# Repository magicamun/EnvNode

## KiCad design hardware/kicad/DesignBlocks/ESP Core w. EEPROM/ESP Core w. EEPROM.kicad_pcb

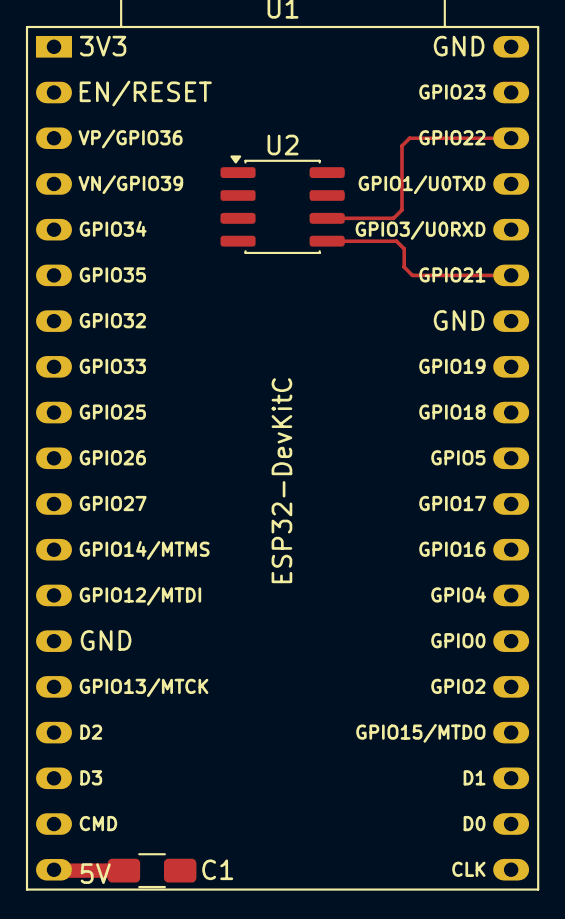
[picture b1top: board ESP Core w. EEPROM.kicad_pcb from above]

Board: 2 copper layers, 3 parts (0 on the bottom side), 4 nets.

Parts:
C1: 100nF; C_1206_3216Metric_Pad1.33x1.80mm_HandSolder
U1: ESP32-DevKitC
U2: 24LC32; SOIC-8_3.9x4.9mm_P1.27mm

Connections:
+5V: C1.1, U1.19 (5V)
GND: C1.2, U1.14 (GND), U1.32 (GND), U1.38 (GND), U2.1 (A0), U2.2 (A1), U2.3 (A2), U2.4 (GND), U2.7 (WP)
I2C0_SCL: U1.36 (GPIO22), U2.6 (SCL)
I2C0_SDA: U1.33 (GPIO21), U2.5 (SDA)

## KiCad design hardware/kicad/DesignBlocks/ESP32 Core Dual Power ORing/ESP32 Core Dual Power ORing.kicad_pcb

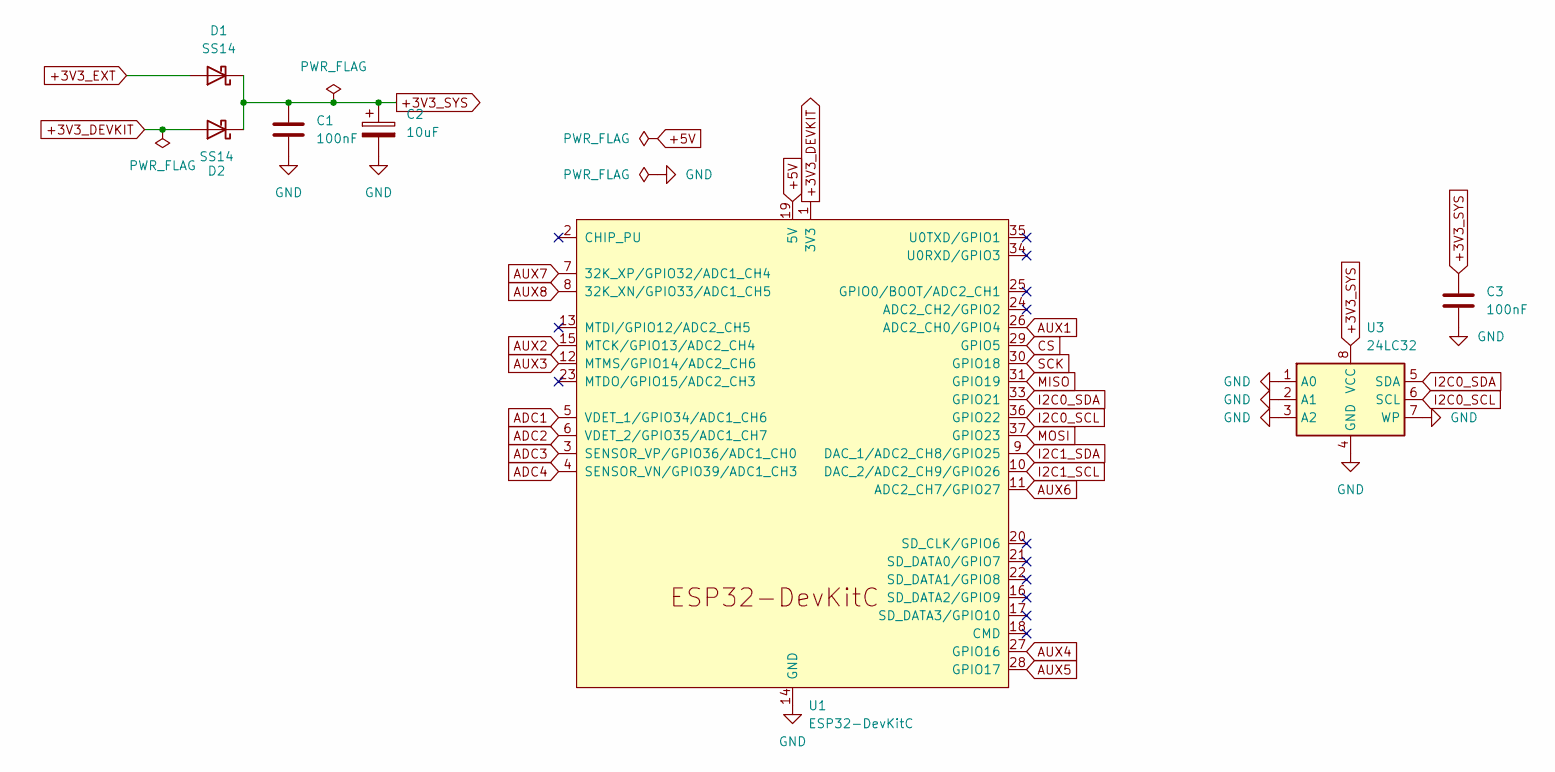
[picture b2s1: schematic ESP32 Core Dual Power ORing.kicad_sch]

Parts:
C1, C3: 100nF; C_1206_3216Metric_Pad1.33x1.80mm_HandSolder
C2: 10uF; CP_Elec_5x5.4
D1, D2: SS14; D_SMA
U1: ESP32-DevKitC
U3: 24LC32; SOIC-8_3.9x4.9mm_P1.27mm

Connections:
+3V3_DEVKIT: D2.2 (A), U1.1 (3V3)
+3V3_EXT: D1.2 (A)
+3V3_SYS: C1.1, C2.1, C3.1, D1.1 (K), D2.1 (K), U3.8 (VCC)
+5V: U1.19 (5V)
ADC1: U1.5 (VDET_1/GPIO34/ADC1_CH6)
ADC2: U1.6 (VDET_2/GPIO35/ADC1_CH7)
ADC3: U1.3 (SENSOR_VP/GPIO36/ADC1_CH0)
ADC4: U1.4 (SENSOR_VN/GPIO39/ADC1_CH3)
AUX1: U1.26 (ADC2_CH0/GPIO4)
AUX2: U1.15 (MTCK/GPIO13/ADC2_CH4)
AUX3: U1.12 (MTMS/GPIO14/ADC2_CH6)
AUX4: U1.27 (GPIO16)
AUX5: U1.28 (GPIO17)
AUX6: U1.11 (ADC2_CH7/GPIO27)
AUX7: U1.7 (32K_XP/GPIO32/ADC1_CH4)
AUX8: U1.8 (32K_XN/GPIO33/ADC1_CH5)
CS: U1.29 (GPIO5)
GND: C1.2, C2.2, C3.2, U1.14 (GND), U1.32 (GND), U1.38 (GND), U3.1 (A0), U3.2 (A1), U3.3 (A2), U3.4 (GND), U3.7 (WP)
I2C0_SCL: U1.36 (GPIO22), U3.6 (SCL)
I2C0_SDA: U1.33 (GPIO21), U3.5 (SDA)
I2C1_SCL: U1.10 (DAC_2/ADC2_CH9/GPIO26)
I2C1_SDA: U1.9 (DAC_1/ADC2_CH8/GPIO25)
MISO: U1.31 (GPIO19)
MOSI: U1.37 (GPIO23)
SCK: U1.30 (GPIO18)

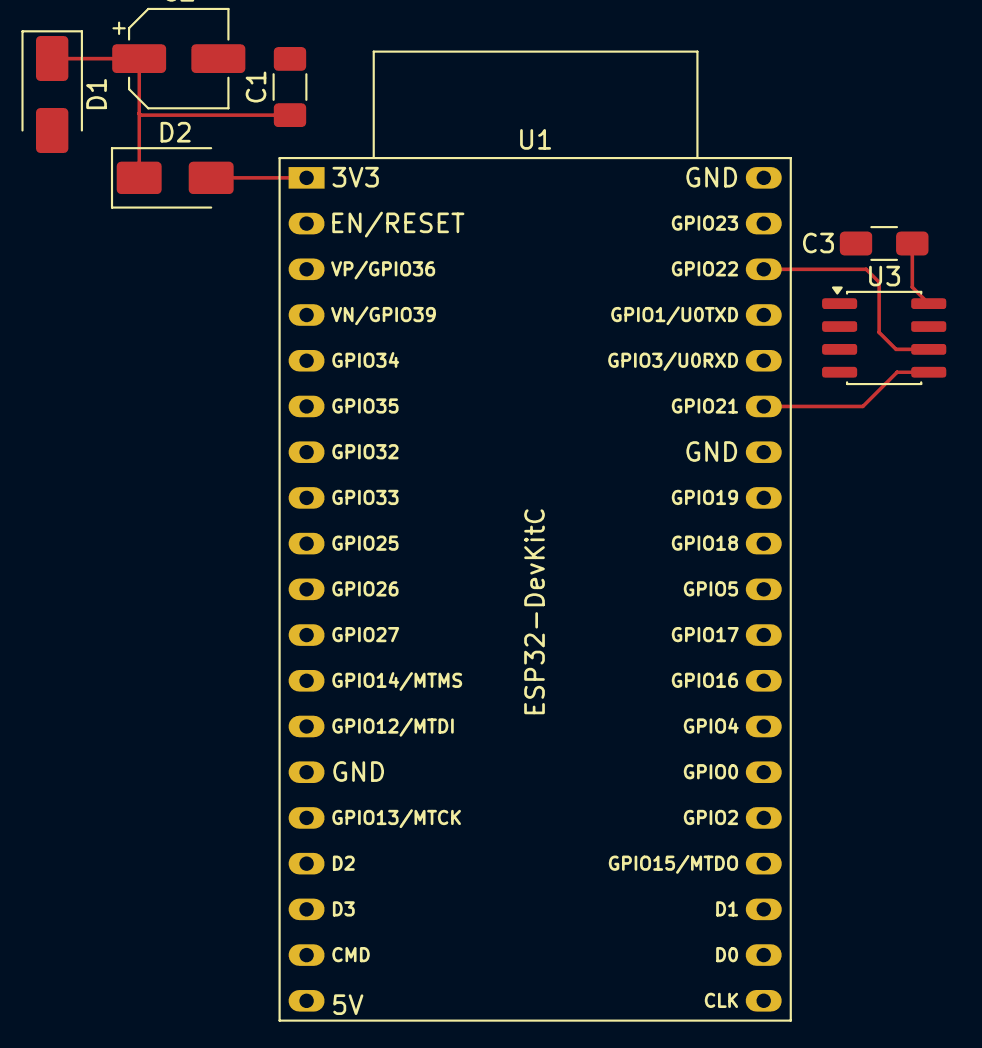
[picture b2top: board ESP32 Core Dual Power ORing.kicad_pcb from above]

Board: 2 copper layers, 7 parts (0 on the bottom side), 5 nets.

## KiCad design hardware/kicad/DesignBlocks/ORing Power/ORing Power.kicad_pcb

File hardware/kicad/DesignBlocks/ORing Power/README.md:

# ORing Power Module

The ORing Power module is a 39 mm x 15 mm castellated daughterboard for EnvNode mainboards. It combines the external 5 V input, the 3.3 V regulator, and the diode ORing between the regulator output and the ESP32 DevKit 3.3 V rail. Mainboards use the matching carrier footprint and no longer need to reproduce this circuit locally.

## Project and Library Items

- Editable KiCad project: `hardware/kicad/DesignBlocks/ORing Power/`
- Published design block: `hardware/kicad/Libraries/EnvNodeDesignBlocks.kicad_blocks/ORing Power.kicad_block/`
- Mainboard symbol: `EnvNode-Symbols:ORingPower_Module`
- Module footprint: `EnvNode-Footprints:ORingPower_Module_Castellated`
- Mainboard carrier footprint: `EnvNode-Footprints:ORingPower_Carrier`
- Assembly and bring-up guide: `Documentation/ORing_Power_Bestueckungs_und_Bringup_Rev0.1.pdf`

The symbol defaults to the carrier footprint. The ORing Power PCB itself overrides that assignment with the module-side castellated footprint.

## Electrical Function

The module accepts 5 V through either the two-pin JST-PH connector or the USB-C connector. These two 5 V inputs share the same `+5V` net and are not isolated from one another. Do not connect independent supplies to both connectors unless they are explicitly suitable for direct parallel operation.

The LM3940 generates `+3V3_EXT` from `+5V`. Two SS14 Schottky diodes combine `+3V3_EXT` and the mainboard-provided `+3V3_DEVKIT` rail into `+3V3_SYS`. The topology prevents either 3.3 V source from feeding back into the other through the ORing path.

The USB-C connector is the six-contact, power-only GCT `USB4125-GF-A-0190`. `CC1` and `CC2` each have their own 5.1 kΩ pull-down resistor to GND. The connector does not expose USB data signals and does not implement USB Power Delivery negotiation; it requests the standard USB-C 5 V source mode only.

## Castellated Interface

| Pin | Net | Module direction | Function |
| ---: | --- | --- | --- |
| 1 | `GND` | Common | Ground |
| 2 | `+5V` | Output to mainboard | Shared 5 V input rail |
| 3 | `+3V3_EXT` | Output to mainboard | LM3940 regulator output before ORing diode |
| 4 | `+3V3_DEVKIT` | Input from mainboard | ESP32 DevKit 3.3 V source before ORing diode |
| 5 | `+3V3_SYS` | Output to mainboard | ORed system 3.3 V rail |

Pin numbers, net names, pad positions, and module orientation are contractual. A carrier PCB must use the matching carrier footprint without moving individual pads.

## Mechanical Integration

The module is soldered directly onto the mainboard using the five castellated edge pads. The carrier footprint reserves the 39 mm x 15 mm module outline and provides matching mainboard pads. Before releasing a mainboard, verify:

- the module outline and nearby component courtyards do not overlap;
- the USB-C opening is reachable at the intended enclosure edge;
- sufficient solder fillet is accessible at every castellated pad;
- no mainboard copper, vias, or components occupy the reserved module area; and
- the assembly process supports castellated-hole soldering on the selected PCB finish and thickness.

The castellated-hole geometry must be confirmed with the PCB manufacturer before the first production order. Fabrication outputs must identify the edge-plated half holes correctly; ordinary routed holes without edge plating are not an equivalent substitute.

## Component Notes

| Reference | Function | Important assignment |
| --- | --- | --- |
| J3 | USB-C 5 V input | GCT `USB4125-GF-A-0190`; KiCad six-pin power-only footprint |
| R1, R2 | USB-C Rd | 5.1 kΩ each, one resistor per CC pin |
| J1 | Alternate 5 V input | JST `B2B-PH-SM4-TB`, two-pin, vertical SMD; KiCad footprint `JST_PH_B2B-PH-SM4-TB_1x02-1MP_P2.00mm_Vertical` |
| U1 | 3.3 V regulator | `LM3940IMP-3.3/NOPB`, SOT-223 |
| D1, D2 | 3.3 V source ORing | SS14, SMA |
| C1, C5 | Local bypass | 100 nF, 1206 |
| C2 | Regulator output capacitor | 10 µF electrolytic, `CP_Elec_5x5.4`; polarity required |
| C3 | 5 V input capacitor | 10 µF ceramic, 1206 |
| C4 | System rail bulk capacitor | 47 µF tantalum, EIA-3528-21; polarity required |

## Mainboard Use

1. Place `EnvNode-Symbols:ORingPower_Module` in the mainboard schematic.
2. Keep its default `EnvNode-Footprints:ORingPower_Carrier` footprint.
3. Connect all five named rails according to the interface table.
4. Update the PCB from the schematic and place the complete carrier footprint at the intended board edge.
5. Remove the former discrete ORing-power circuit and verify that no duplicate regulator, diode, USB-C, or input components remain.
6. Run ERC, PCB/schematic parity, DRC, and a visual 3D/mechanical review on the completed mainboard.

Do not place the module-side castellated footprint on the mainboard. Do not use the carrier footprint as the outline of a separately fabricated ORing Power PCB.

## Validation Status

Checked with KiCad 10 on 2026-09-21:

- schematic ERC: 0 errors, 0 warnings;
- PCB DRC: 0 violations and 0 unconnected items;
- all seven electrical nets have zero unrouted connections;
- USB VBUS, GND, shield, CC1, and CC2 map to the expected footprint pads;
- the GCT USB4125 footprint is aligned with the PCB edge; and
- the editable source and published library block are synchronized.

This validation covers design consistency, not physical manufacture. The first fabricated module still requires continuity, polarity, 5 V input, 3.3 V regulation, source handover, reverse-current, thermal, USB-C insertion, and castellated-solder-joint tests.

## Documentation verification — 2026-10-05

The Revision 0.1 assembly guide now carries current PCB, schematic, and parts-workbook hashes. The PCB has no formal title-block revision; 0.1 is the existing documentation designation. Compared with the previously documented PCB, only plot settings, an empty settings block, and serialization order changed; board geometry and circuitry are unchanged. The existing 3D reference view remains valid.

The guide previously swapped the diode references in its functional description and tests: D1 connects `+3V3_EXT` to `+3V3_SYS`, while D2 connects `+3V3_DEVKIT` to `+3V3_SYS`. These references are corrected. PCB pad nets were checked against an exported schematic netlist and matched. This documentation check did not repeat full ERC/DRC or physical testing.

## PCB patch 0.1.1 (18 October 2026)

The PCB now has a formal title block with revision 0.1.1 and front-silkscreen
labels for the module and the two-pin JST-PH 5 V input. J1 pin 1 remains GND;
pin 2 remains +5V. All other PCB data, including copper, pad geometry, components,
board outline and mounting geometry, is identical to the previous committed PCB.
The existing Revision 0.1 assembly guide remains applicable; this patch requires
no mainboard profile change or reprovisioning. See the shared
[PCB patch convention](../../../../docs/BoardIdentityRecord.md).

The 5 October verification above describes the earlier source snapshot. No new
ERC/DRC or physical qualification is claimed by this silkscreen-only update.
The published library design block remains at its earlier snapshot; it has not
been republished with these labels. No new 3D illustration was generated.

## Illustrated edge-pad test points (18 October 2026)

The assembly PDF includes an additional landscape reference page for all five U2
castellated pads, their nets and the standalone-module measurement conditions.
The [web guide](../../../../docs/site/mainboards/oring-power/index.md) contains the
same overview and test-point table. Measurements use U2.1 / GND as their reference.
The native PCB/STEP render omits the unavailable J1 housing model; its actual
footprint remains visible. See [render provenance and sources](../../../../images/oring-power/testpoints/README.md).

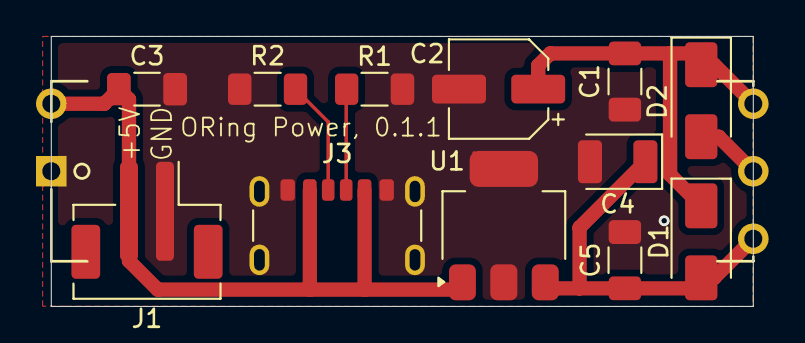
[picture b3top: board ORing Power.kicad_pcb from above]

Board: 2 copper layers, 39.0 x 15.0 mm, 13 parts (0 on the bottom side), 7 nets.

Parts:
C1, C5: 100nF; C_1206_3216Metric_Pad1.33x1.80mm_HandSolder
C2: 10uF; CP_Elec_5x5.4
C3: 10uF; C_1206_3216Metric_Pad1.33x1.80mm_HandSolder
C4: 47uF; CP_EIA-3528-21_Kemet-B
D1, D2: SS14; D_SMA
J1: Conn_01x02_Pin; JST_PH_B2B-PH-SM4-TB_1x02-1MP_P2.00mm_Vertical
J3: USB_C_Receptacle_PowerOnly_6P; USB_C_Receptacle_GCT_USB4125-xx-x-0190_6P_TopMnt_Horizontal
R1, R2: 5,1kOhm; R_1206_3216Metric_Pad1.30x1.75mm_HandSolder
U1: LM3940IMP-3.3/NOPB; SOT-223-3_TabPin2
U2: ORingPower_Module; ORingPower_Module_Castellated

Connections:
+3V3_DEVKIT: D2.2 (A), U2.4 (+3V3_DEVKIT)
+3V3_EXT: C4.1, C5.2, D1.2 (A), U1.3 (OUT), U2.3 (+3V3_EXT)
+3V3_SYS: C1.1, C2.1, D1.1 (K), D2.1 (K), U2.5 (+3V3_SYS)
+5V: C3.1, J1.2, J3.A9 (VBUS), J3.B9 (VBUS), U1.1 (IN), U2.2 (+5V)
GND: C1.2, C2.2, C3.2, C4.2, C5.1, J1.1, J3.A12 (GND), J3.B12 (GND), J3.SH (SHIELD), R1.2, R2.2, U1.2 (GND), U2.1 (GND)
unnamed: J3.A5 (CC1), R2.1
unnamed: J3.B5 (CC2), R1.1
